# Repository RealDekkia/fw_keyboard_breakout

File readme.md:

# Framework Laptop Input Cover Adapter

[![CC BY-NC-SA 4.0][cc-by-nc-sa-shield]][cc-by-nc-sa]

This is an Adapter-PCB for the [Keyboard-Input connector](https://github.com/FrameworkComputer/Framework-Laptop-13/blob/main/Electrical/Pinouts.md#input-cover-interface) on the 13" Framework Laptop.

It aims to create a more convenient way to Power up the Board compared to the small button on the PCB itself. It also has pins for a USB 2.0 connection, because why not?

This work is licensed under a
[Creative Commons Attribution-NonCommercial-ShareAlike 4.0 International License][cc-by-nc-sa].

[![CC BY-NC-SA 4.0][cc-by-nc-sa-image]][cc-by-nc-sa]

[cc-by-nc-sa]: http://creativecommons.org/licenses/by-nc-sa/4.0/
[cc-by-nc-sa-image]: https://licensebuttons.net/l/by-nc-sa/4.0/88x31.png
[cc-by-nc-sa-shield]: https://img.shields.io/badge/License-CC%20BY--NC--SA%204.0-lightgrey.svg

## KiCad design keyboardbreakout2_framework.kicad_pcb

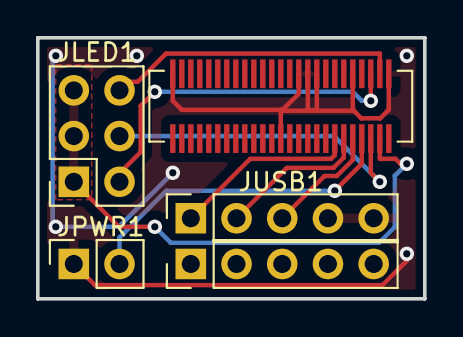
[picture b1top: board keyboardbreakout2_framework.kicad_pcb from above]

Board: 2 copper layers, 21.5 x 14.5 mm, 4 parts (0 on the bottom side), 9 nets.

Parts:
JLED1: Conn_02x03_Odd_Even; PinSocket_2x03_P2.54mm_Vertical
JPWR1: Conn_01x02; PinSocket_1x02_P2.54mm_Vertical
JUSB1: Conn_01x05; PinSocket_1x05_P2.54mm_Vertical
U1: 10156001-051100LF

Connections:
+5V: JLED1.1, JLED1.3, JLED1.5, U1.27
GND: JPWR1.1, JUSB1.4, JUSB1.5, U1.1, U1.15, U1.16, U1.17, U1.21, U1.25, U1.38
unnamed: JPWR1.2, U1.29
unnamed: JUSB1.1, U1.32
unnamed: JUSB1.2, U1.31
unnamed: JUSB1.3, U1.30
unnamed: JLED1.2, U1.23
unnamed: JLED1.6, U1.24
unnamed: JLED1.4, U1.28

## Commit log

2023-04-14 created readme
2023-04-14 added license
2023-04-14 added second row to usb-headers because most adapters on amazon have two rows (only one connector works tho)
2023-04-14 added screenshot to readme
2023-04-14 updated gitignore
2023-04-14 added connector for power-button LEDs

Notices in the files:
parts and their libraries:
Copyright 2021 Accelerated Designs. All rights reserved.
